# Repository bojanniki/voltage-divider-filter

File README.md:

# Voltage divider with RC filter and zener protection

A small measurement board that turns a 9 V battery (6 to 9.6 V) into a filtered, protected output of about 4.4 V, using only two resistors, a capacitor and a zener diode (no op-amp).

This is a **simulation and design project**: calculation in Python (Jupyter), simulation in LTspice, schematic and PCB in KiCad. Nothing was built or measured.

What the project covers: the voltage divider and its Thevenin equivalent, loading of the divider, the RC filter time constant, tolerances (worst case and Monte Carlo), a non-ideal component (zener leakage), and the full flow from calculation to simulation, schematic, PCB and manufacturing files.

## Circuit

| Ref | Part | Value |
|---|---|---|
| R1 | resistor, 1 % | 120 kΩ |
| R2 | resistor, 1 % | 100 kΩ |
| C1 | ceramic capacitor | 100 nF |
| D1 | zener diode | BZX55C5V1 (5.1 V) |
| TP1 to TP3 | test points | BAT+, VOUT, GND |
| J1 | screw terminal, 2 pins | battery input (BAT_IN) |
| J2 | pin header, 2 pins | output (GND, VOUT) |

Nets: `BAT+` (J1-1, R1, TP1), `VOUT` (R1, R2, C1, D1 cathode, TP2, J2-2), `GND` (J1-2, R2, C1, D1 anode, TP3, J2-1).

**How it works.** R1 and R2 divide the battery voltage with ratio 0.4545. Seen from the output, the divider is a source in series with R_th = R1 ∥ R2 = 54.5 kΩ, and everything connected to the output interacts with this resistance: C1 forms an RC low-pass filter with it, any load pulls the output down through it, and the zener leakage current flows through it. D1 does not conduct in normal operation (the output stays below 4.4 V); it limits the output only if the input voltage rises abnormally.

## Results

All values at 9.6 V unless stated otherwise. Calculation: [`notebook/01_divider_calculation.ipynb`](notebook/01_divider_calculation.ipynb).

| Quantity | Value |
|---|---|
| Divider ratio | 0.4545 |
| Output voltage, no load | 4.364 V at 9.6 V, 2.727 V at 6 V |
| Quiescent current | 43.6 µA |
| Power in R1 / R2 | 0.23 mW / 0.19 mW (more than 1000x below the 1/4 W rating) |
| Thevenin resistance | 54.55 kΩ |
| Time constant, cutoff (no load) | 5.45 ms, 29.2 Hz |
| Worst case, 1 % resistors | 4.316 to 4.411 V |
| Worst case, 5 % resistors | 4.127 to 4.603 V |
| Monte Carlo, normal distribution (σ = tol/3) | σ = 11.3 mV (1 %), 56.3 mV (5 %) |
| Output with load 1 MΩ / 100 kΩ / 10 kΩ | 4.138 V / 2.824 V / 0.676 V |
| Cutoff with 10 kΩ load | 188 Hz |

### Why the output drops under load

A load R_L sits in parallel with R2, so the output becomes V_th · R_L / (R_L + R_th) and the relative error is about R_th / (R_L + R_th). For an error below 5 % the load must be at least 19 · R_th, about 1.04 MΩ. With a 10 kΩ load the output collapses to 0.68 V, and the filter also stops filtering (cutoff rises from 29 Hz to 188 Hz). The divider can only feed a high-impedance input.

### Tolerances

The worst case (all resistors at their limits at once) is guaranteed but pessimistic. The Monte Carlo run (10 000 samples) shows the spread for a normal and a uniform distribution of the resistor values; the mean stays at the nominal 4.364 V, so tolerances cause scatter but no systematic offset.

### Zener leakage

The datasheet specifies a maximum reverse current of 0.1 µA at 25 °C, measured at 1 V, which corresponds to an error of 5.5 mV at the output. It does not specify the leakage at 4.4 V, so this is a reference value, not a bound for the operating point. The LTspice model gives a leakage that depends on one model parameter (`Nbv`, the sharpness of the knee): 5 pA, 3.3 nA and 0.3 µA for `Nbv` = 1, 2, 3, which corresponds to 0.0003 mV, 0.18 mV and 16.6 mV at the output. The real value at 4.4 V can only be found by measuring real parts.

## Python vs LTspice

LTspice 26.1.1, schematics in [`ltspice/`](ltspice/), exported data and logs in [`ltspice/data/`](ltspice/data/). The full table is in [`docs/comparison_table.md`](docs/comparison_table.md).

For the purely resistive circuit (DC sweep of the battery voltage, load sweep, operating point) the two tools agree to better than 10⁻⁴ (relative); the remaining difference comes from the 6 to 7 significant digits of the exported data. Three differences are larger, and each has a specific cause:

| Quantity | Python | LTspice | Difference | Cause |
|---|---|---|---|---|
| Time constant | 5.4545 ms | 5.458 ms | +0.07 % | threshold of the `.meas` rounded to 3.762 V (exact 3.7617 V) |
| Cutoff, no load | 29.178 Hz | 29.179 Hz | +0.0014 % | threshold of the `.meas` rounded |
| Cutoff, 10 kΩ load | 188.33 Hz | 188.38 Hz | +0.025 % | threshold of the `.meas` rounded |

The zener results are not comparable one to one: the datasheet gives a maximum at 1 V, the model gives a number that depends on a model parameter. Also note that with the default solver tolerance the nA-level leakage current at `Nbv` = 2 came out about 22 % too low; the zener schematic therefore uses `.options reltol=1e-6`.

## PCB

Two-layer through-hole board, TODO mm × TODO mm. Signal traces (0.4 mm) on the top layer, ground pour on the bottom layer. ERC and DRC pass without errors. Test points and connectors sit on the board edge.

Manufacturing files are in [`kicad/output/`](kicad/output/): Gerber files and Excellon drill file in `gerber/`, bill of materials in `bom.csv`.

## Repository structure

```
voltage-divider-filter/
├── README.md
├── notebook/      calculation notebook (Python, Jupyter)
├── ltspice/       LTspice schematics; data/ has exported data and logs
├── kicad/         KiCad project; output/ has Gerber, drill and BOM
├── figures/       plots generated by the notebook
└── docs/          schematic, 3D view, comparison table
```

## Reproducing the results

- **Calculation:** Python 3 with NumPy, Matplotlib and Jupyter. Run the notebook from the `notebook/` folder, since it reads `../ltspice/data/` and writes to `../figures/`.
- **Simulation:** open the `.asc` files in LTspice. In `05_zener.asc` the `.step` runs `Nbv` = 1, 2, 3 and the `.meas` results appear in the SPICE output log.
- **PCB:** open `kicad/voltage_divider.kicad_pro` in KiCad (version TODO).

## What this project does not prove

Nothing was measured on a real board, so validation is a comparison of two models. A real board would have component tolerances, parasitics and noise that the simulation does not see. This is a deliberate trade-off.

## If this board were actually built

These are engineering suggestions that follow from the results above; none of them has been designed or simulated here.

- **Reverse polarity.** A battery connected the wrong way round is the most likely mistake with a screw terminal. A series Schottky diode is the simplest protection but drops about 0.2 to 0.4 V, which shifts the output (a 0.3 V drop lowers it by about 0.14 V because of the divider ratio); a P-channel MOSFET in series drops much less but needs more parts. A keyed battery connector helps as well, together with clear polarity marks on the silkscreen.
- **Fuse.** A resettable (PTC) fuse in series with BAT+ would protect the wiring and the battery against assembly faults. Note that R1 itself limits a short circuit at VOUT to about 80 µA at 9.6 V, so the fuse covers faults on the board, not load shorts.
- **Measuring the output.** A 10 MΩ multimeter loads the output by R_th / (10 MΩ + R_th) = 0.54 %, comparable to the resistor tolerance. Either correct for it or add a buffer (phase 5: an op-amp follower, which would also remove the loading problem shown above).
- **Zener.** Measure the leakage at 4.4 V on real parts; if it is too large, choose a zener with a higher breakdown voltage if the protected input allows it. The clamp is soft: in the simulation the output reaches only about 4.85 V at a 15 V input because R1 limits the zener current, so it is protection against overvoltage, not a precise limit.
- **Component choice.** Ceramic disc capacitors can have a wide tolerance and a strong dependence on voltage and temperature, which moves the cutoff frequency; a C0G/NP0 or film capacitor would be better. With 0.1 % resistors the output spread would shrink by about ten times if accuracy matters.
- **Manufacturing.** Check the design rules of the chosen fabricator (minimum clearance, edge clearance) against the DRC settings, and add mounting holes if the board is to be fixed to an enclosure.

## Phase 5 (later)

After the op-amp chapter, an LM358 voltage follower can be added behind the divider; the same load plot is then repeated to show what the buffer fixes.

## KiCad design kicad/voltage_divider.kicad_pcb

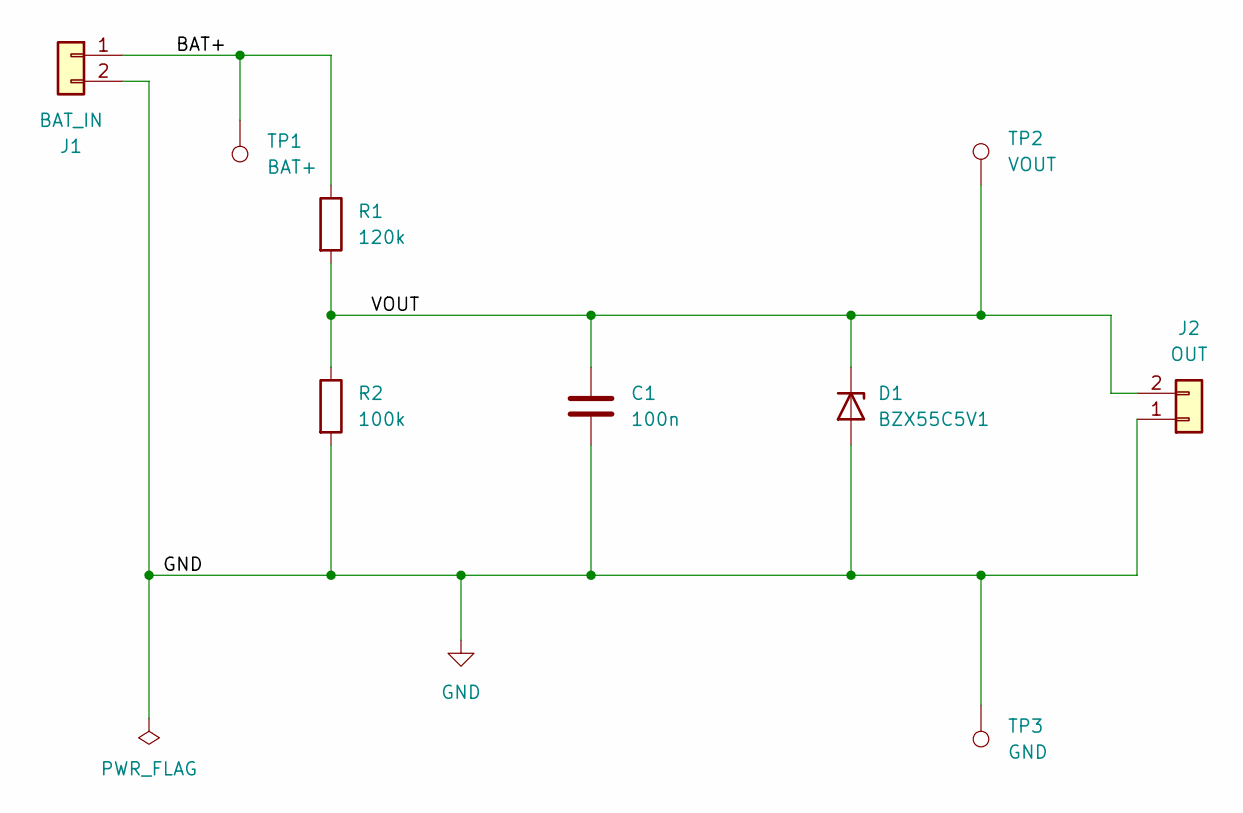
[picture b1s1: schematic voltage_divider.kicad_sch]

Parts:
C1: 100n; C_Disc_D5.0mm_W2.5mm_P5.00mm
D1: BZX55C5V1; D_DO-35_SOD27_P7.62mm_Horizontal
J1: BAT_IN; TerminalBlock_Phoenix_MKDS-1,5-2-5.08_1x02_P5.08mm_Horizont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
J2: OUT; PinHeader_1x02_P2.54mm_Vertical
R1: 120k; R_Axial_DIN0207_L6.3mm_D2.5mm_P10.16mm_Horizontal
R2: 100k; R_Axial_DIN0207_L6.3mm_D2.5mm_P10.16mm_Horizontal
TP1: BAT+; TestPoint_THTPad_D2.0mm_Drill1.0mm
TP2: VOUT; TestPoint_THTPad_D2.0mm_Drill1.0mm
TP3: GND; TestPoint_THTPad_D2.0mm_Drill1.0mm

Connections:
/BAT+: J1.1, R1.1, TP1.1 (1_1)
/VOUT: C1.1, D1.1 (K), J2.2, R1.2, R2.1, TP2.1 (1_1)
GND: C1.2, D1.2 (A), J1.2, J2.1, R2.2, TP3.1 (1_1)

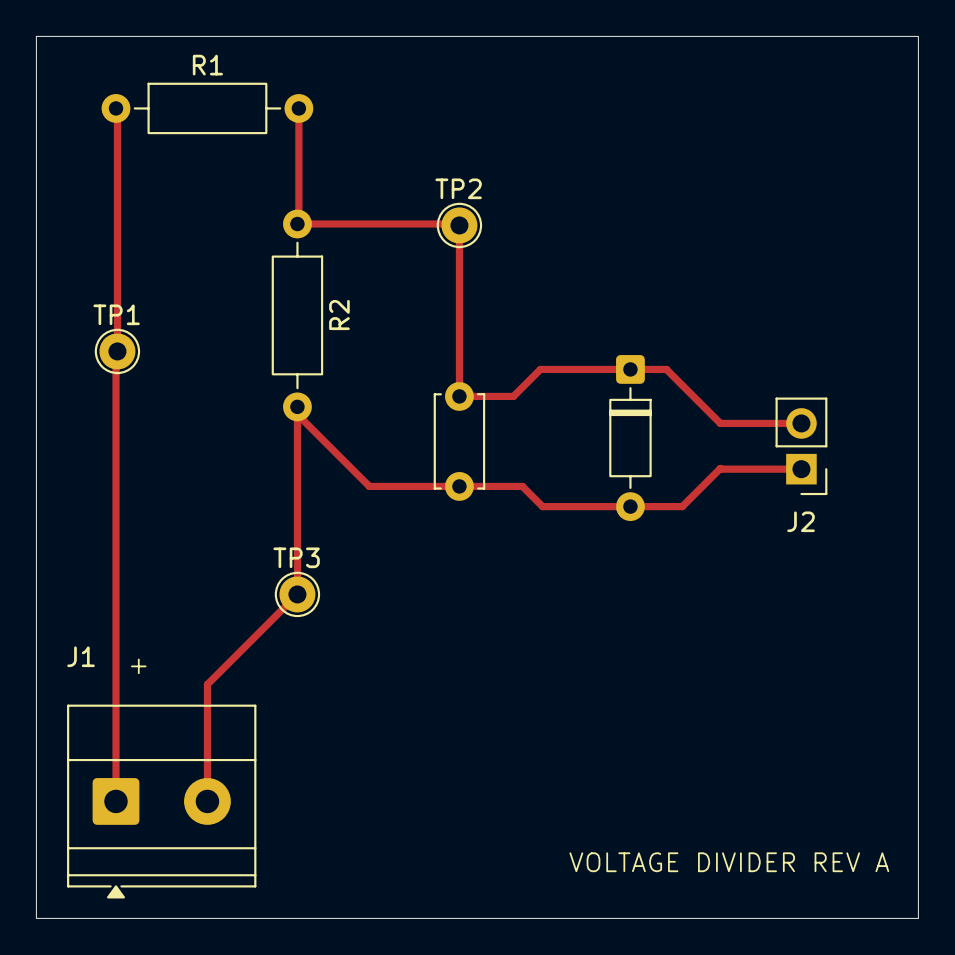
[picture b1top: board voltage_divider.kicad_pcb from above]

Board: 2 copper layers, 49.0 x 49.0 mm, 9 parts (0 on the bottom side), 3 nets.
